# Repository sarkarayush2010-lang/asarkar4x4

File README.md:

# asarkar4x4
A 4x4 macropad with an oled display! Calculator-inspired case and numpad firmware with a fully customizable OLED!!!

===========================================================================================

Img1: Full Macropad Assembly. PCB components including keys and Oled screen not in cad file. 

Img2: PCB Front

Img3: PCB Back

Img4: Schematic

Img5: how Case fits together(it's pretty obvious anyways but sandwich method!)

===========================================================================================

Features:
Translucent case(or not if you choose to print in a non-translucent filament, but why not transparent tech???)

128x32 OLED Display

16 (yes SIXTEEN) fully customizable keys(thats like enough to play minecraft)

and ITS MY FIRST PCB YAY!!!

===========================================================================================
Bill of Materials:

16x Cherry MX Switches

16x DSA Keycaps

4x M3x5x4 Heatset inserts

4x M3x16mm SHCS Bolts

PCB

1x 0.91" 128x32 OLED Display

20x 1N4148 DO-35 Diodes.

1x XIAO RP2040

1x Case(2x 3d-printed parts)

That should be all!
Theres still an extra gpio pin, so maybe u could hardwire something else like an led or something cool in the future!

===========================================================================================

CAD Model:
Everything fits together using 5 M3 Bolts and heatset inserts. You can just use a soldering iron for those!

Prints in two peices, and the parts use a SANDWICH MOUNT to hold the PCB in place. 

Oled and microcontroller have a little display window. It is not filled in with anything, but you can use those clear boxes that you get when you buy strawberries and cut those and hot glue it to the top of the case to look cool! 

Made in onshape

===========================================================================================

PCB:
Made in Ki-CAD

It's my first PCB! It uses 20 diodes

===========================================================================================

Firmware

Uses Basic QMK Firmware for everything.

Firmware given is just for the keypad. Oled is for you(and me) to make later! Or just leave the oled blank lol.

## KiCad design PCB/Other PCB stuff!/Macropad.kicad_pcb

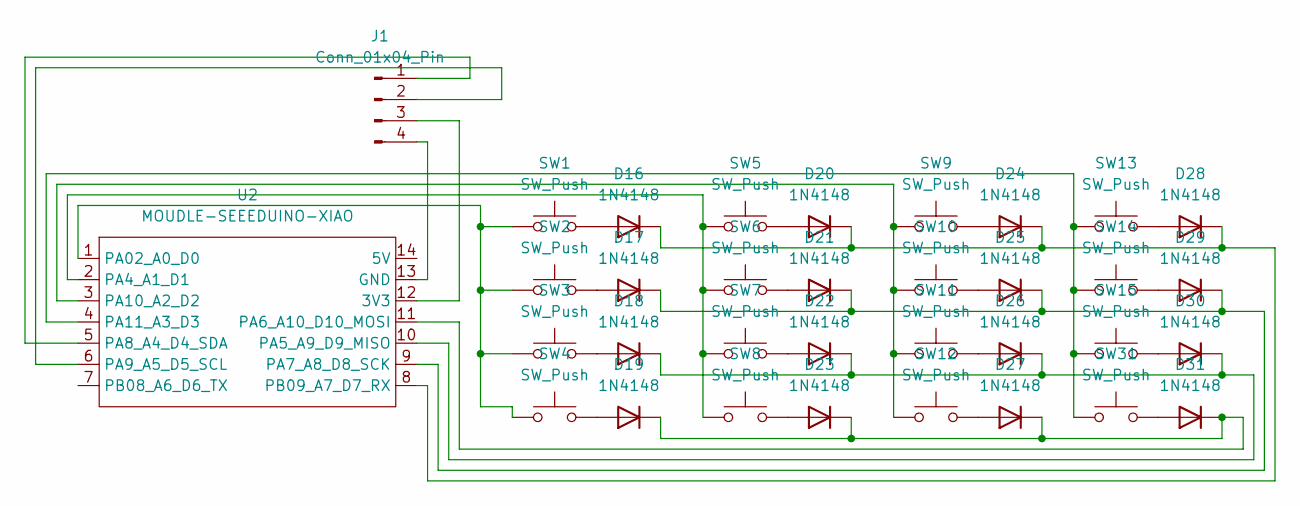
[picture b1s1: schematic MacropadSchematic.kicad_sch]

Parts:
D16, D17, D18, D19, D20, D21, D22, D23, D24, D25, D26, D27, D28, D29, D30, D31: 1N4148; D_DO-35_SOD27_P7.62mm_Horizontal
J1: Conn_01x04_Pin; PinHeader_1x04_P2.54mm_Vertical
SW1, SW2, SW3, SW4, SW5, SW6, SW7, SW8, SW9, SW10, SW11, SW12, SW13, SW14, SW15, SW31: SW_Push; SW_Cherry_MX_1.00u_PCB
U2: MOUDLE-SEEEDUINO-XIAO; XIAO-Generic-Hybrid-14P-2.54-21X17.8MM

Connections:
unnamed: D16.2 (A), SW1.2
unnamed: D16.1 (K), D20.1 (K), D24.1 (K), D28.1 (K), U2.8 (PB09_A7_D7_RX)
unnamed: D17.2 (A), SW2.2
unnamed: D17.1 (K), D21.1 (K), D25.1 (K), D29.1 (K), U2.9 (PA7_A8_D8_SCK)
unnamed: D18.2 (A), SW3.2
unnamed: D18.1 (K), D22.1 (K), D26.1 (K), D30.1 (K), U2.10 (PA5_A9_D9_MISO)
unnamed: D19.2 (A), SW4.2
unnamed: D19.1 (K), D23.1 (K), D27.1 (K), D31.1 (K), U2.11 (PA6_A10_D10_MOSI)
unnamed: D20.2 (A), SW5.2
unnamed: D21.2 (A), SW6.2
unnamed: D22.2 (A), SW7.2
unnamed: D23.2 (A), SW8.2
unnamed: D24.2 (A), SW9.2
unnamed: D25.2 (A), SW10.2
unnamed: D26.2 (A), SW11.2
unnamed: D27.2 (A), SW12.2
unnamed: D28.2 (A), SW13.2
unnamed: D29.2 (A), SW14.2
unnamed: D30.2 (A), SW15.2
unnamed: D31.2 (A), SW31.2
unnamed: J1.1, U2.5 (PA8_A4_D4_SDA)
unnamed: J1.2, U2.6 (PA9_A5_D5_SCL)
unnamed: J1.3, U2.12 (3V3)
unnamed: J1.4, U2.13 (GND)
unnamed: SW1.1, SW2.1, SW3.1, SW4.1, U2.1 (PA02_A0_D0)
unnamed: SW5.1, SW6.1, SW7.1, SW8.1, U2.2 (PA4_A1_D1)
unnamed: SW9.1, SW10.1, SW11.1, SW12.1, U2.3 (PA10_A2_D2)
unnamed: SW13.1, SW14.1, SW15.1, SW31.1, U2.4 (PA11_A3_D3)

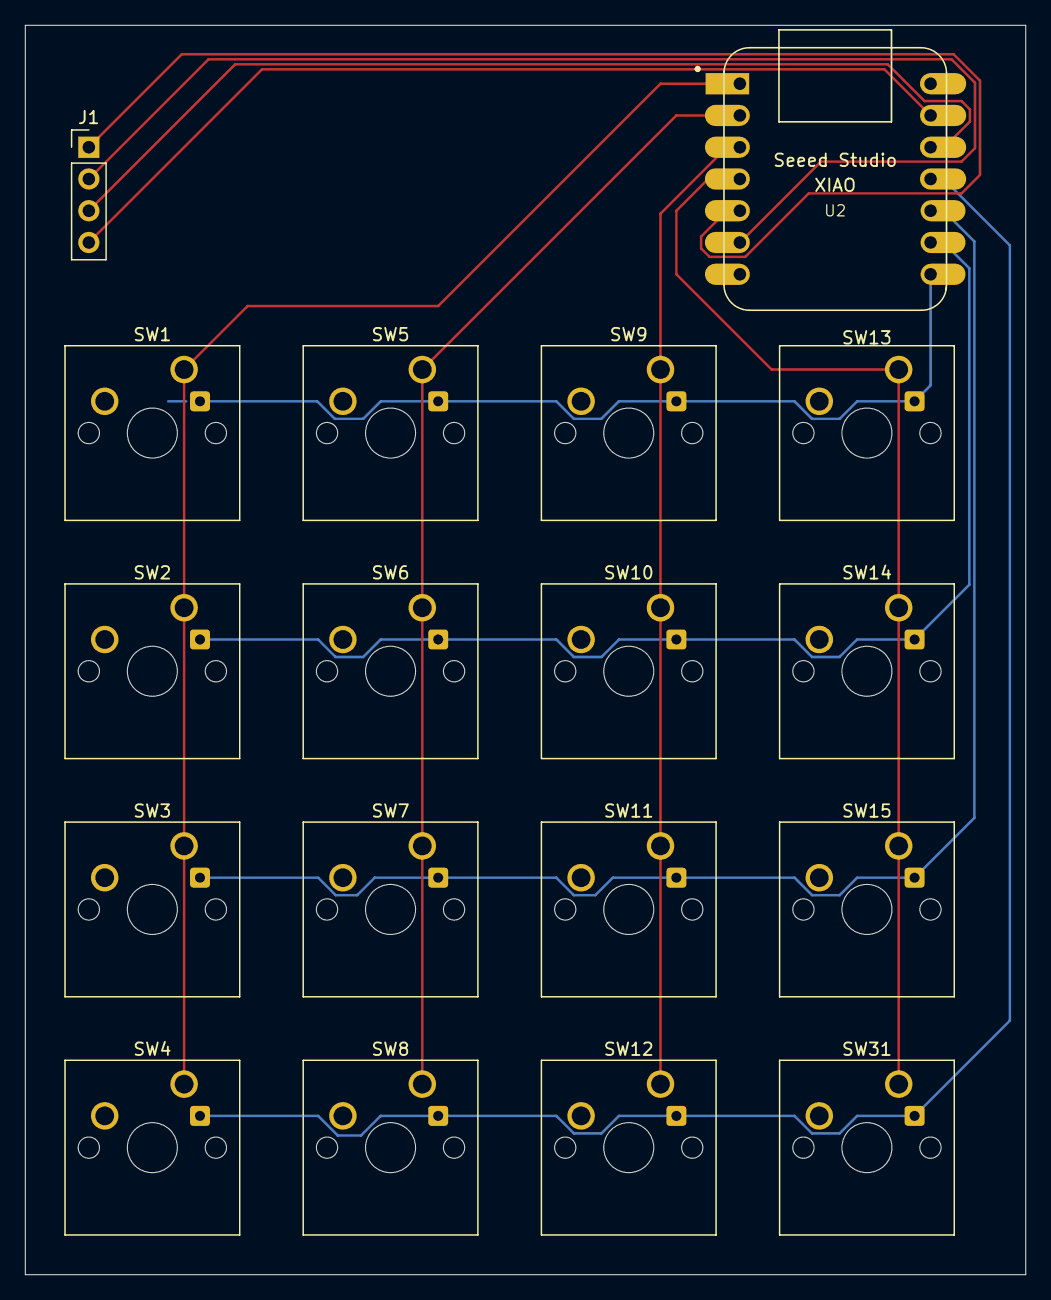
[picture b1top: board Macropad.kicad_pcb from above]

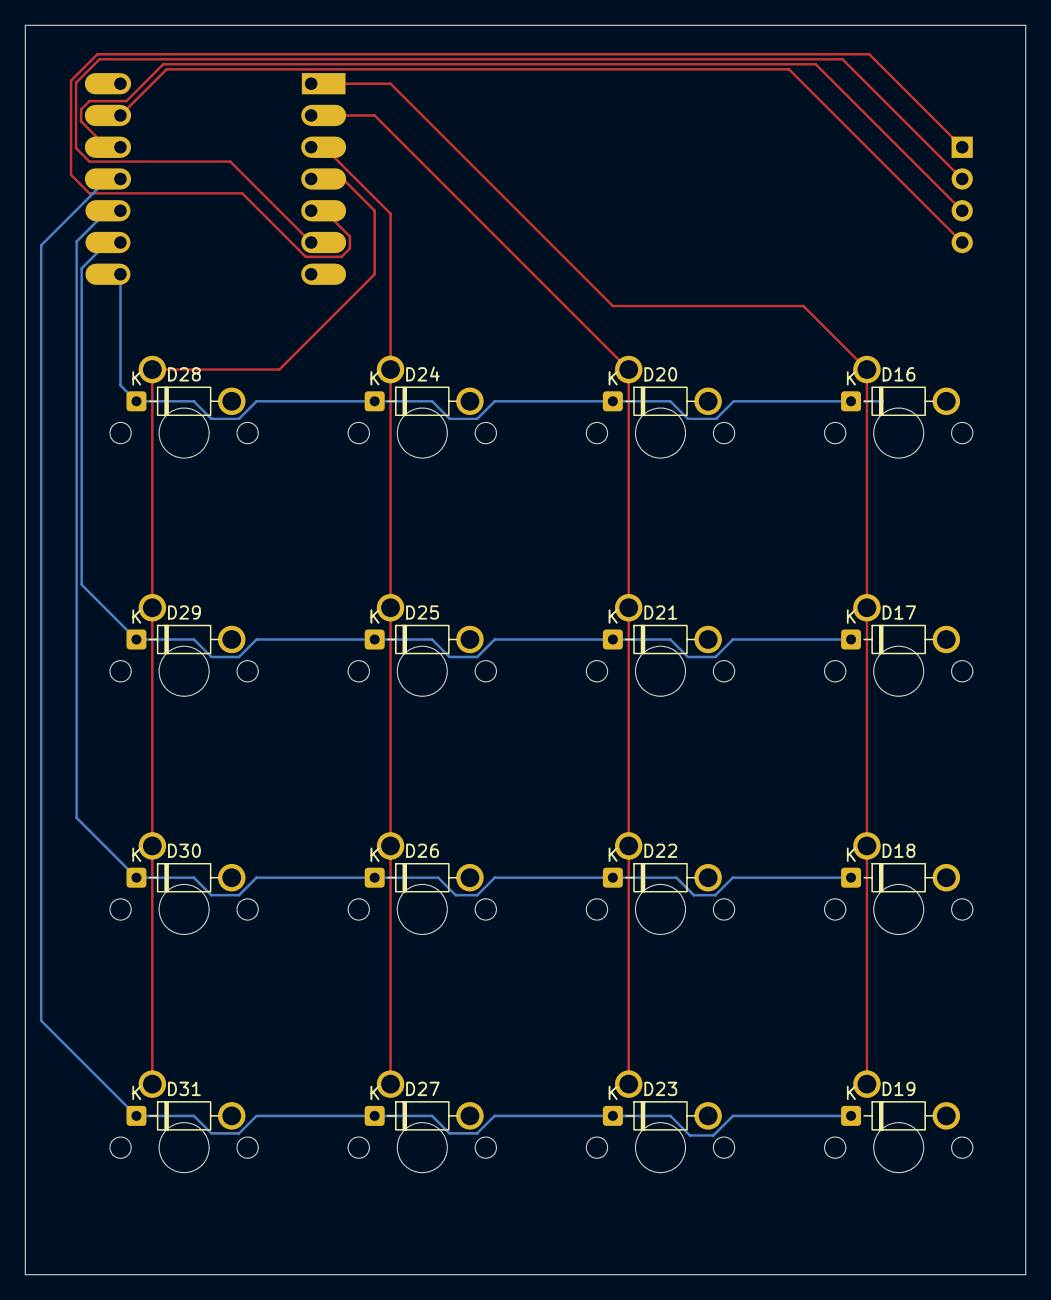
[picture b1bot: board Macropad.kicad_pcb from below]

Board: 2 copper layers, 80.0 x 99.9 mm, 34 parts (16 on the bottom side), 28 nets.

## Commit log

2026-03-31 README.md
